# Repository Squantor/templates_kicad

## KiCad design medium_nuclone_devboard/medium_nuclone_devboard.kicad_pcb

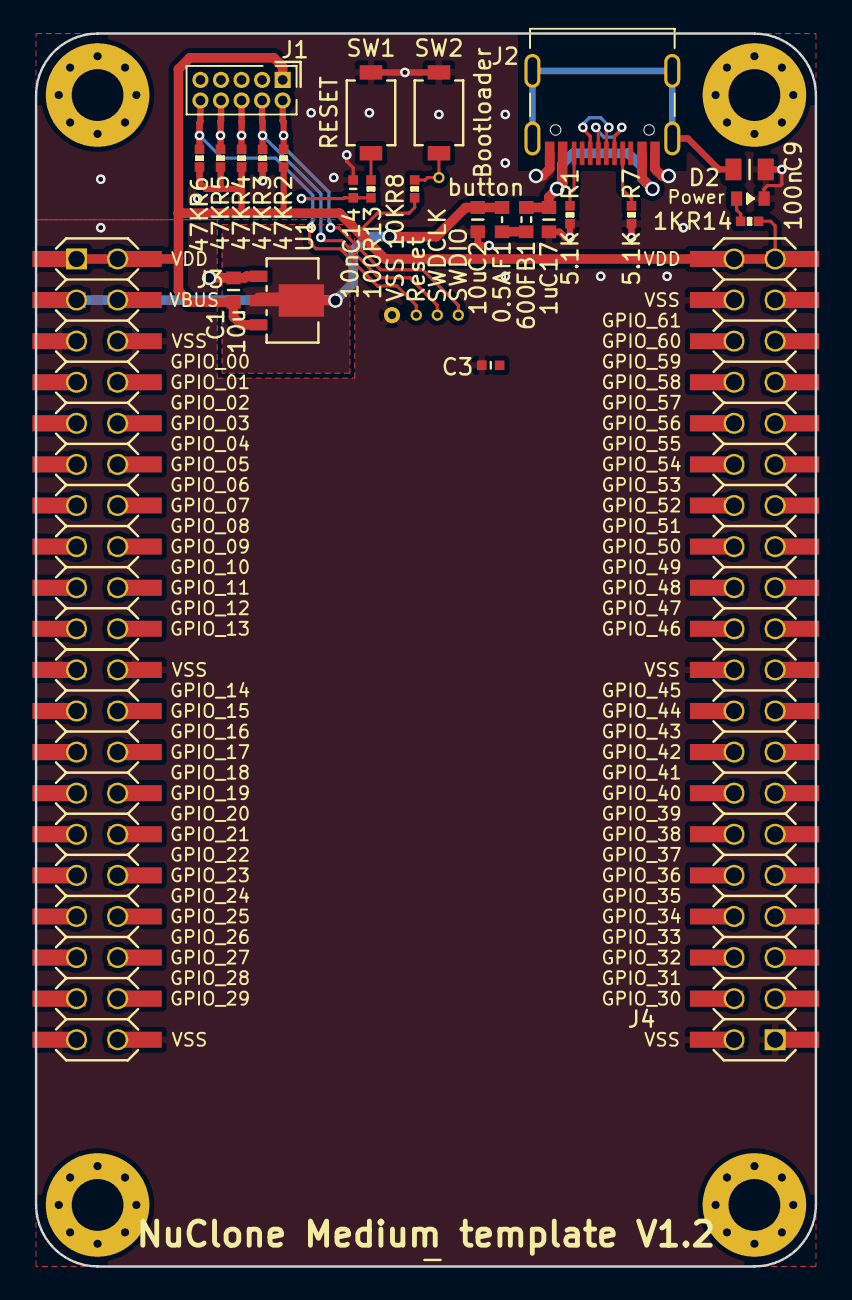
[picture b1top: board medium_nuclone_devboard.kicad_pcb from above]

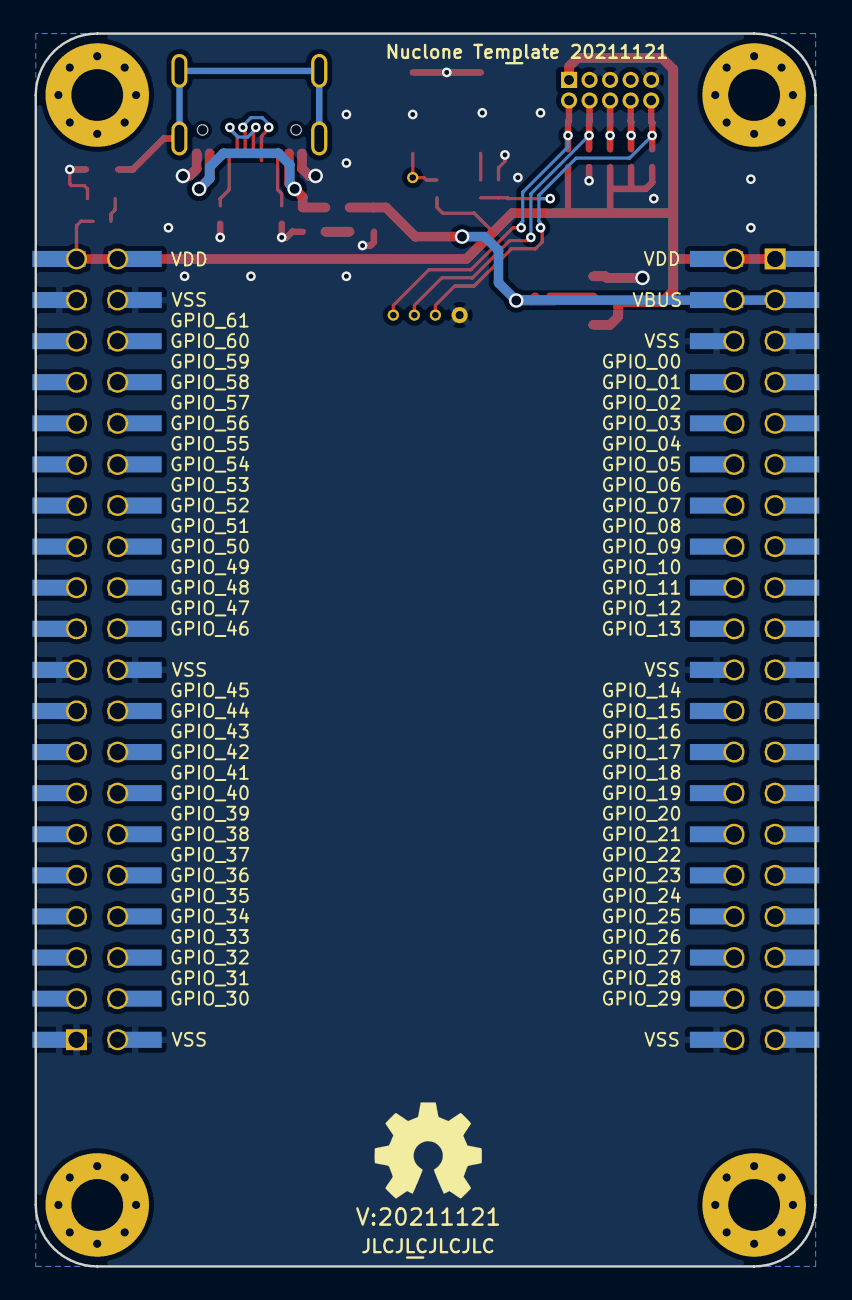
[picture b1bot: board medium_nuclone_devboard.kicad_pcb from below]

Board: 2 copper layers, 48.2 x 76.2 mm, 40 parts (4 on the bottom side), 18 nets.

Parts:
C1, C2: 10u; C_0603
C3: 1u; C_0402
C9: 100n; C_0805
C14: 10n; C_0402
C17: 1u; C_0603
D2: GREEN; LED_0603_hand
F1: 0.5A; F_0603_hand
FB1: 600; L_0603
H1, H2, H3, H4: MountingHole; MountingHole_3.2mm_M3_Pad_Via
J1: JTAG_2X05; Header-0127-2X05-H006
J2: TYPE-C-31-M-12; USB-C-HRO-31-M-12
J3: nuclone_medium_left; nuclone_medium_left_stacked
J4: nuclone_medium_right; nuclone_medium_right_stacked
N1: OHWLOGO; OSHW-Symbol_6.7x6mm_SilkScreen
N2: 20211121; Label_version
N3: JLCJLCJLCJLC; Label_Generic
N4: NuClone Medium template V1.2; Label_Generic
N5: Nuclone Template 20211121; Label_Generic
R1, R7: 5.1K; R_0402_hand
R2, R3, R4, R5, R6: 47K; R_0402_hand
R8: 10K; R_0402_hand
R13: 100; R_0402_hand
R14: 1K; R_0402_hand
SW1: RESET; TD-85XU
SW2: Bootloader; TD-85XU
TP1: SWDIO; TestPoint_hole_H04R07
TP2: SWDCLK; TestPoint_hole_H04R07
TP3: VSS; TestPoint_hole_H05R10
TP4: button; TestPoint_hole_H04R07
TP5: Reset; TestPoint_hole_H04R07
U1: MCP1702-MB; SOT89-NXP

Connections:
/Bootloader: R8.1, SW2.2, TP4.1
/RESET: C14.2, J1.10, R6.1, R13.1, TP5.1
/TCK: J1.4, R3.1, TP2.1
/TDI: J1.8, R5.1
/TDO: J1.6, R4.1
/TMS: J1.2, R2.1, TP1.1
/VBUS: C2.2, F1.1, J3.3, J3.4, U1.2
/VDD: C1.1, C3.1, J1.1, J3.1, J3.2, J4.39, J4.40, R2.2, R4.2, R5.2, R6.2, R8.2, R14.2, U1.3
/VSS: C1.2, C2.1, C3.2, C9.1, C14.1, C17.1, D2.1, J1.3, J1.5, J1.9, J2.A1B12, J2.B1A12, J3.5, J3.6, J3.21, J3.22, J3.39, J3.40, J4.1, J4.2, J4.19, J4.20, J4.37, J4.38, R1.1, R3.2, R7.1, SW1.1, SW2.1, TP3.1, U1.1
unnamed: C9.2, J2.S
unnamed: C17.2, FB1.2, J2.A4B9, J2.B4A9
unnamed: D2.2, R14.1
unnamed: F1.2, FB1.1
unnamed: J2.A5, R7.2
unnamed: J2.A6, J2.B6
unnamed: J2.A7, J2.B7
unnamed: J2.B5, R1.2
unnamed: R13.2, SW1.2

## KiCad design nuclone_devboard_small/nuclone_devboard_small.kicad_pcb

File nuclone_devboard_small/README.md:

# Nuclone development board template for low pincount microcontrollers
Small development board inspired by the nucleo series from STM32.
## TODO's
Still some things need to be done:
* proper description(TODO)
* schematic entry (TODO)
* PCB layout (TODO)
* Review with one night in between (TODO)
* Produce at [OSHPARK](https://oshpark.com/) (TODO)
* Assemble (TODO)
* Test & characterise (TODO)
* update Readme.md with pictures and BOM (TODO)

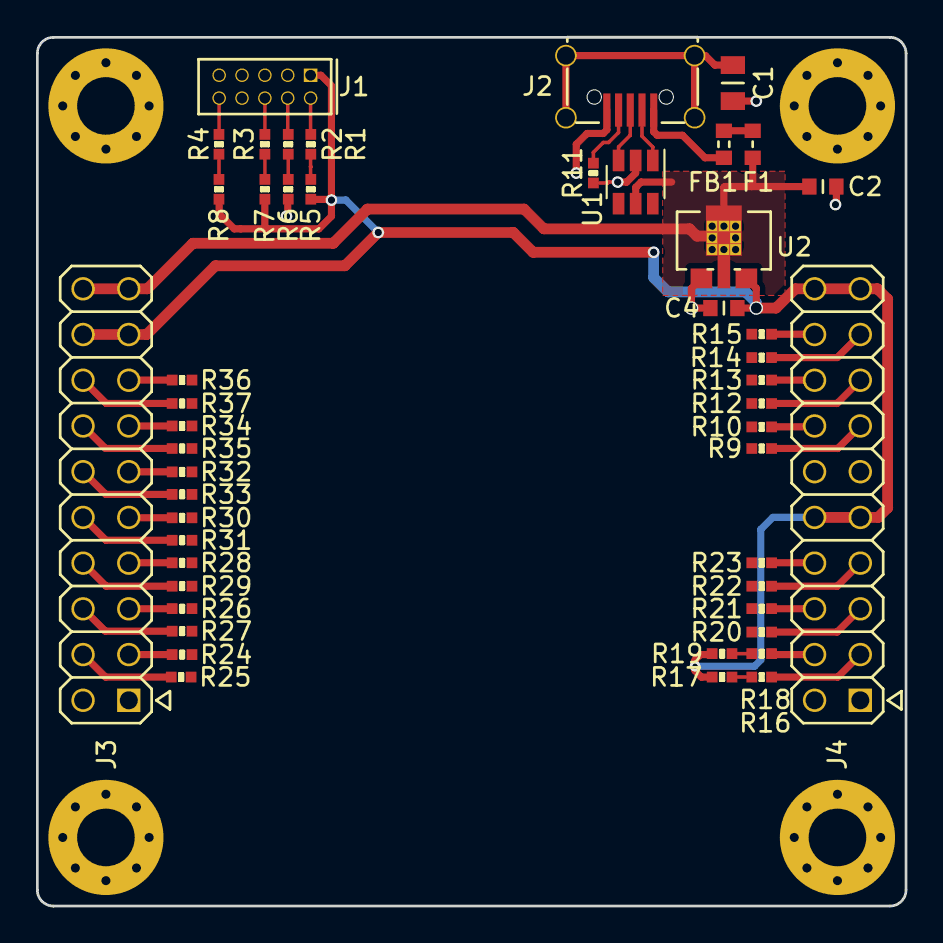
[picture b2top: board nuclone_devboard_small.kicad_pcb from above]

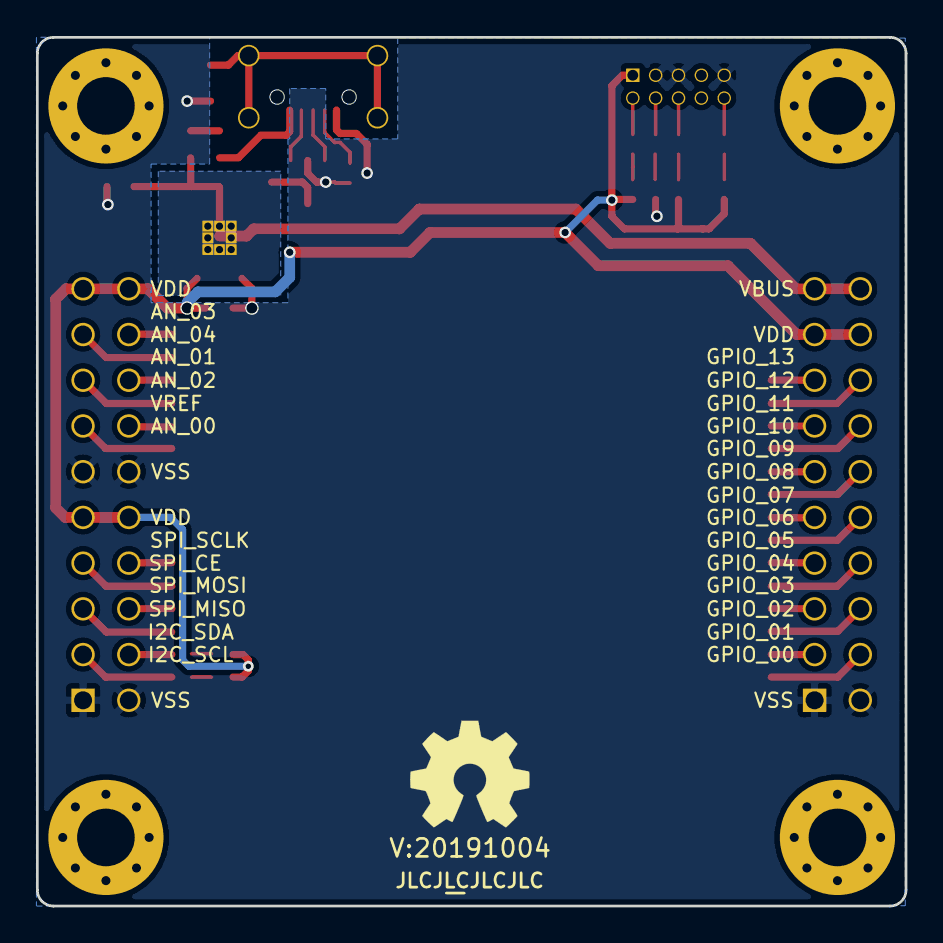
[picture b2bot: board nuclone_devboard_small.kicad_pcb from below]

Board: 2 copper layers, 48.3 x 48.3 mm, 55 parts (3 on the bottom side), 45 nets.

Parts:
C1: 100n; C_0805
C2, C4: 10u; C_0603
F1: 0.5A; F_0603_hand
FB1: 100; L_0603
H1, H2, H3, H4: MountingHole; MountingHole_3.2mm_M3_Pad_Via
J1: JTAG_2X05; Header-0127-2X05-H006
J2: USB-ID; USB-muB-SMD_TH
J3: nuclone_20pin_gpio; Nuclone_20pin_gpio
J4: nuclone_20pin_bus_analog; Nuclone_20pin_bus_analog
N1: OHWLOGO; OSHW-Symbol_6.7x6mm_SilkScreen
N2: 20191004; Label_version
N3: JLCJLCJLCJLC; Label_Generic
R1, R2, R3, R4, R9, R10, R12, R13, R14, R15, R16, R18, R20, R21, R22, R23, R24, R25, R26, R27, R28, R29, R30, R31, R32, R33, R34, R35, R36, R37: 100; R_0402_hand
R5: 100K; R_0402_hand
R6, R7, R8: 100k; R_0402_hand
R11: 0; R_0402_hand
R17, R19: 2.2K; R_0402_hand
U1: USBLC6-2; SOT23-6-HAND
U2: MCP1702-MB; SOT89-SOT23-Dual-NXP

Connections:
/AN_00: J4.14, R10.2
/AN_01: J4.15, R12.2
/AN_02: J4.16, R13.2
/AN_03: J4.17, R14.2
/AN_04: J4.18, R15.2
/GPIO_00: J3.3, R24.2
/GPIO_01: J3.4, R25.2
/GPIO_02: J3.5, R26.2
/GPIO_03: J3.6, R27.2
/GPIO_04: J3.7, R28.2
/GPIO_05: J3.8, R29.2
/GPIO_06: J3.9, R30.2
/GPIO_07: J3.10, R31.2
/GPIO_08: J3.11, R32.2
/GPIO_09: J3.12, R33.2
/GPIO_10: J3.13, R34.2
/GPIO_11: J3.14, R35.2
/GPIO_12: J3.15, R36.2
/GPIO_13: J3.16, R37.2
/I2C_SCL: J4.4, R18.2
/I2C_SCL_INT: R18.1, R19.1
/I2C_SDA: J4.3, R16.2
/I2C_SDA_INT: R16.1, R17.1
/RESET: R4.2, R8.2
/SPI_CE: J4.8, R23.2
/SPI_MISO: J4.6, R21.2
/SPI_MOSI: J4.5, R20.2
/SPI_SCLK: J4.7, R22.2
/TCK: R2.2, R6.2
/TDO: R3.2, R7.2
/TMS: R1.2, R5.2
/USB_IN_D+: J2.3, U1.3
/USB_IN_D-: J2.2, U1.1
/VBUS: C2.1, F1.1, J3.19, J3.20, U1.5, U2.2
/VDD: C4.1, J1.1, J3.17, J3.18, J4.9, J4.10, J4.19, J4.20, R5.1, R7.1, R8.1, R17.2, R19.2, U2.3
/VREF: J4.13, R9.2
/VSS: C1.2, C2.2, C4.2, J1.3, J1.5, J1.9, J2.5, J3.1, J3.2, J4.1, J4.2, J4.11, J4.12, R6.1, R11.1, U1.2, U2.1
unnamed: C1.1, J2.S
unnamed: F1.2, FB1.1
unnamed: FB1.2, J2.1
unnamed: J1.2, R1.1
unnamed: J1.4, R2.1
unnamed: J1.6, R3.1
unnamed: J1.10, R4.1
unnamed: J2.4, R11.2

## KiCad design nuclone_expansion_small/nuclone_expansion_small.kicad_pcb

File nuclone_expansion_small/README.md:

# $(HARDWARE_PROJECT) project
Project description goes here.
# HSI (Hardware Software Interface)
This applies to a project that has a embedded software component. Describe what each pin/bus does, what it is connected to, what its function is and some "safe" behaviour when starting up.
## TODO's
Still some things need to be done:
* Fill in this project description
* schematic entry 
* PCB layout
* Review with one night in between
* Produce at [OSHPARK](https://oshpark.com/)
* Assemble
* Test & characterise
* update Readme.md with pictures and BOM
## BOM
This is a list of hardware components. If just mentioned a generic component like a 1K 0402 resistor, just name it as such, free to substitute. If you need some special integrated IC's show some sources like Mouser, Digikey, Farnell, or LCSC
* Generic resistor in 0402 housing with a value
* Generic capacitor in 0603 housing with a value
* Special IC from [LCSC](https://lcsc.com/)
## Pictures

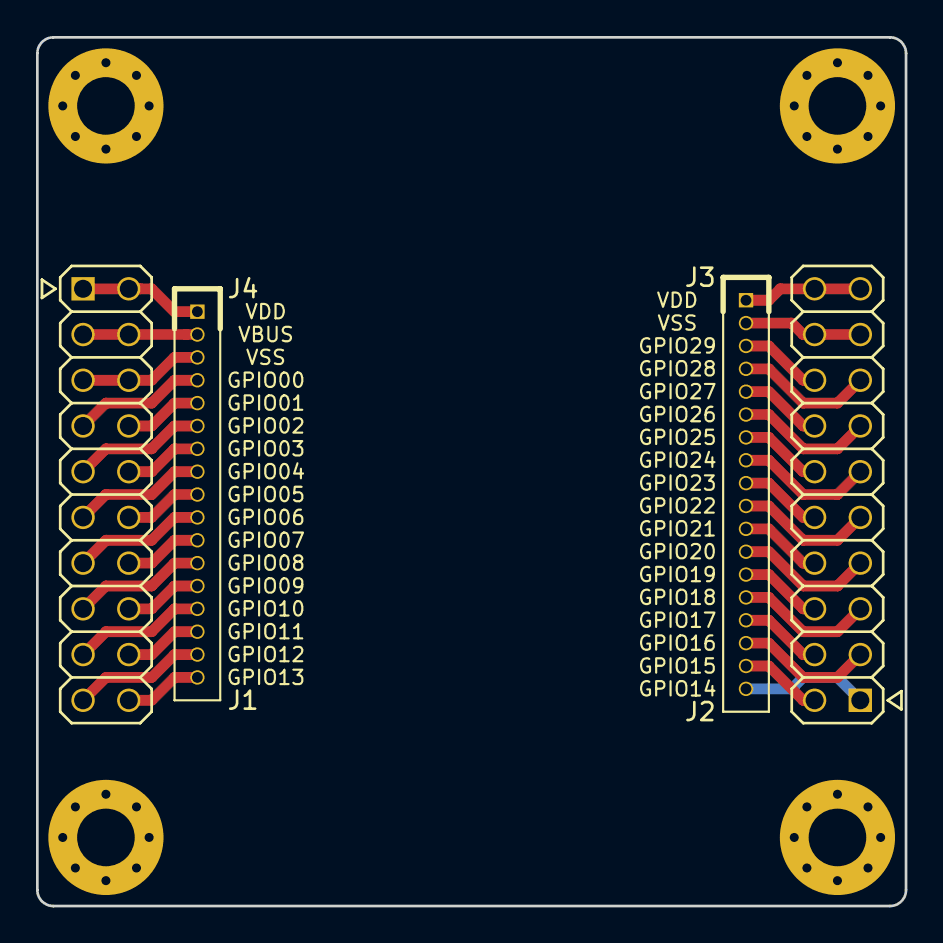
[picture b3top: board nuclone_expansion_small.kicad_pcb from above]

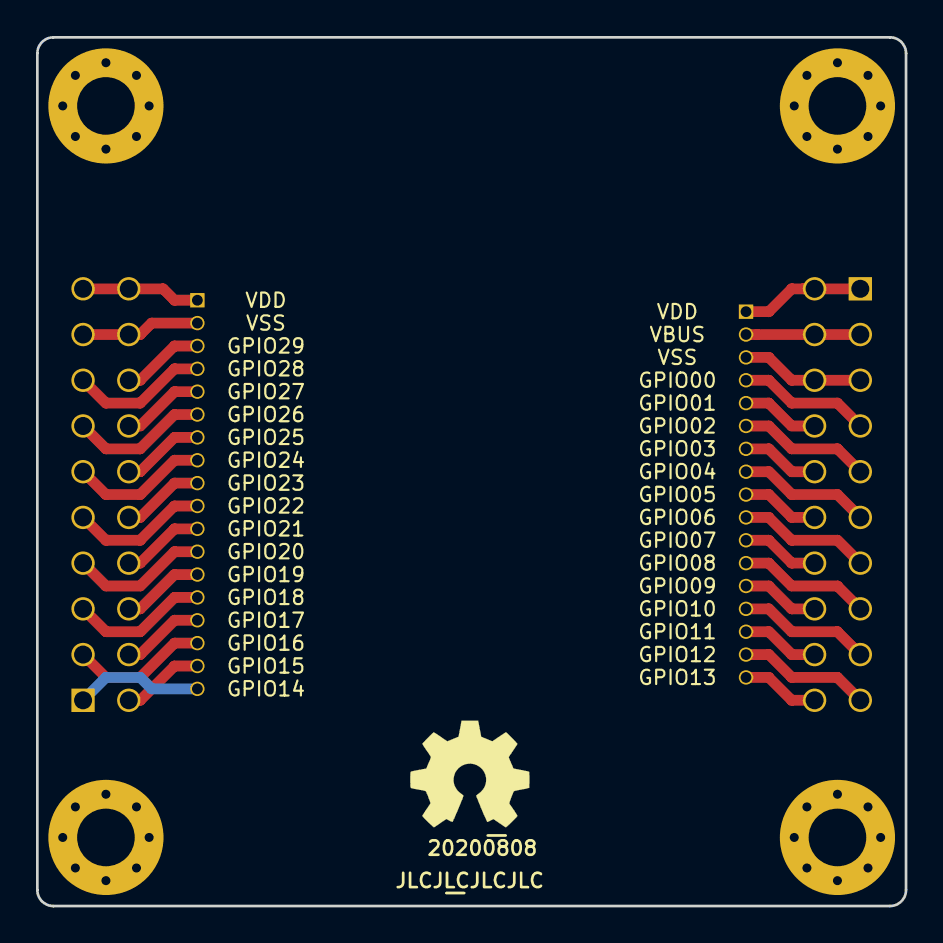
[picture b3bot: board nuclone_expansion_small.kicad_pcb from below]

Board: 2 copper layers, 48.3 x 48.3 mm, 11 parts (3 on the bottom side), 35 nets.

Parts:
H1, H2, H3, H4: MountingHole; MountingHole_3.2mm_M3_Pad_Via
J1: nuclone_small_left; Header-0254-2X10-H010
J2: nuclone_small_right; Header-0254-2X10-H010
J3: PINS_1X18; Header-0127-1X18-H006
J4: PINS_1X17; Header-0127-1X17-H006
N1: OHWLOGO; OSHW-Symbol_6.7x6mm_SilkScreen
N2: 20200808; Label_Generic
N3: JLCJLCJLCJLC; Label_Generic

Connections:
/GPIO_00: J1.7, J4.4
/GPIO_01: J1.8, J4.5
/GPIO_02: J1.9, J4.6
/GPIO_03: J1.10, J4.7
/GPIO_04: J1.11, J4.8
/GPIO_05: J1.12, J4.9
/GPIO_06: J1.13, J4.10
/GPIO_07: J1.14, J4.11
/GPIO_08: J1.15, J4.12
/GPIO_09: J1.16, J4.13
/GPIO_10: J1.17, J4.14
/GPIO_11: J1.18, J4.15
/GPIO_12: J1.19, J4.16
/GPIO_13: J1.20, J4.17
/GPIO_14: J2.1, J3.18
/GPIO_15: J2.2, J3.17
/GPIO_16: J2.3, J3.16
/GPIO_17: J2.4, J3.15
/GPIO_18: J2.5, J3.14
/GPIO_19: J2.6, J3.13
/GPIO_20: J2.7, J3.12
/GPIO_21: J2.8, J3.11
/GPIO_22: J2.9, J3.10
/GPIO_23: J2.10, J3.9
/GPIO_24: J2.11, J3.8
/GPIO_25: J2.12, J3.7
/GPIO_26: J2.13, J3.6
/GPIO_27: J2.14, J3.5
/GPIO_28: J2.15, J3.4
/GPIO_29: J2.16, J3.3
/VBUS: J1.3, J1.4, J4.2
/VDD1: J1.1, J1.2, J4.1
/VDD2: J2.19, J2.20, J3.1
/VSS1: J1.5, J1.6, J4.3
/VSS2: J2.17, J2.18, J3.2

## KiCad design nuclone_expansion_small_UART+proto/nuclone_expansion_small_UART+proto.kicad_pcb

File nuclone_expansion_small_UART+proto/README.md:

# Nuclone expansion board
Nuclone expansion board with UART connector and pin test pads, basis for many development boards
# HSI (Hardware Software Interface)
This applies to a project that has a embedded software component. Describe what each pin/bus does, what it is connected to, what its function is and some "safe" behaviour when starting up.
## TODO's
Still some things need to be done:
* schematic entry 
* Fill in HSI
* PCB layout
* Review with one night in between
* Produce at [Aisler](https://aisler.net/)
* Assemble
* Test & characterise
* update Readme.md with pictures and BOM
## BOM
This is a list of hardware components. If just mentioned a generic component like a 1K 0402 resistor, just name it as such, free to substitute. If you need some special integrated IC's show some sources like Mouser, Digikey, Farnell, or LCSC

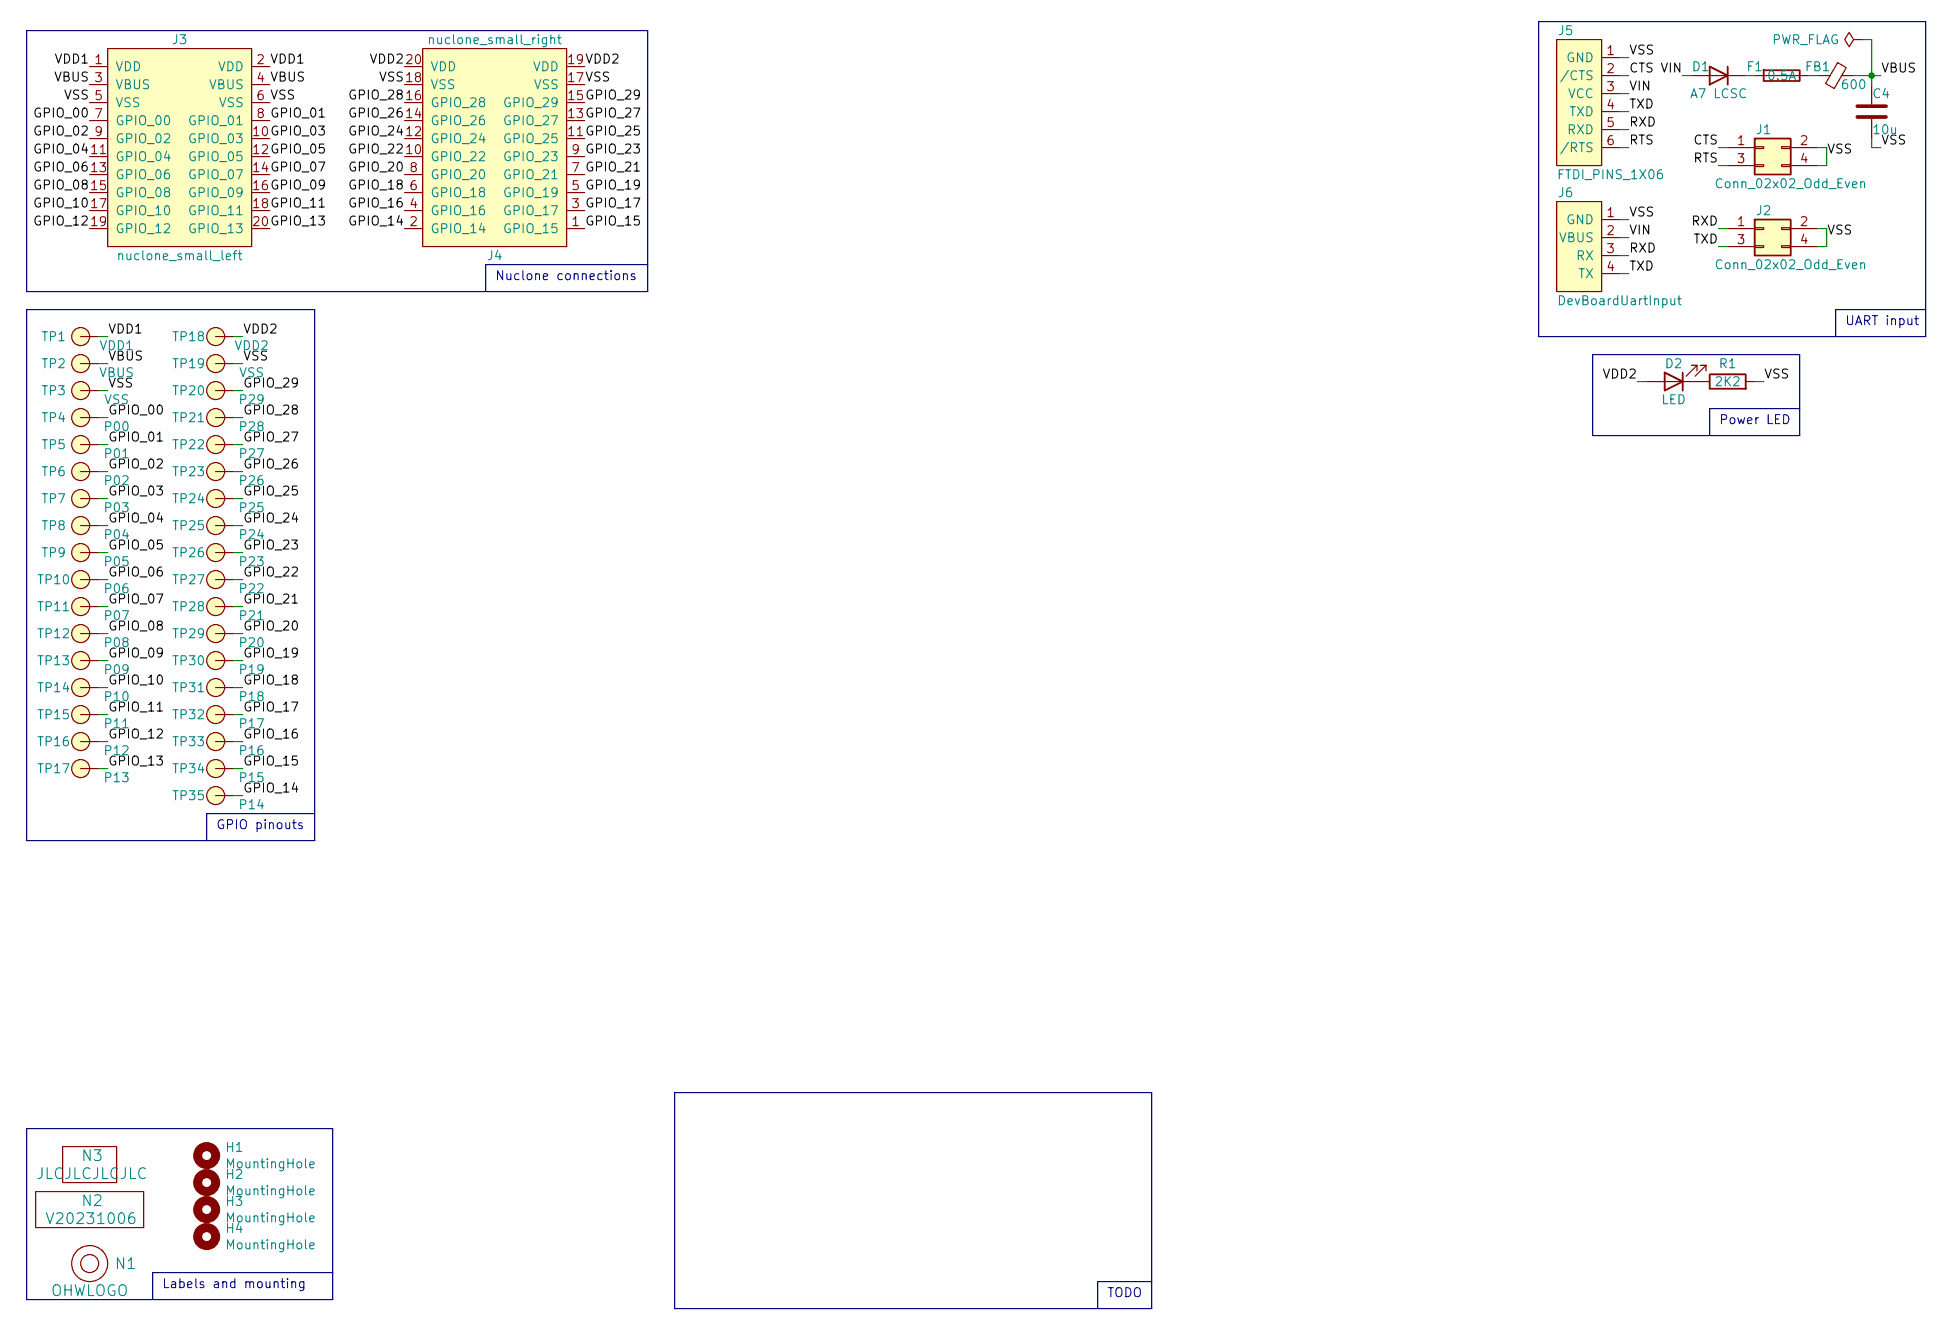
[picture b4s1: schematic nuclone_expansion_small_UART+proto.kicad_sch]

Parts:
C4: 10u; C_0603
D1: A7 LCSC; SOD-123F-hand
D2: LED; LED_0603_hand
F1: 0.5A; F_0603_hand
FB1: 600; L_0603
H1, H2, H3, H4: MountingHole; MountingHole_3.2mm_M3_Pad_Via
J1, J2: Conn_02x02_Odd_Even; Header-0254-2X02-H010
J3: nuclone_small_left; nuclone_small_left_stacked
J4: nuclone_small_right; nuclone_small_right_stacked
J5: FTDI_PINS_1X06; Header-0254-1X06-H010
J6: DevBoardUartInput; JST_PH_B4B-PH-K_1x04_P2.00mm_Vertical
N1: OHWLOGO; OSHW-Symbol_6.7x6mm_SilkScreen
N2: V20231006; Label_Generic
N3: JLCJLCJLCJLC; Label_Generic
R1: 2K2; R_0603_hand
TP1: VDD1; TestPoint_hole_H05R10_2side
TP2: VBUS; TestPoint_hole_H05R10_2side
TP3, TP19: VSS; TestPoint_hole_H05R10_2side
TP4: P00; TestPoint_hole_H05R10_2side
TP5: P01; TestPoint_hole_H05R10_2side
TP6: P02; TestPoint_hole_H05R10_2side
TP7: P03; TestPoint_hole_H05R10_2side
TP8: P04; TestPoint_hole_H05R10_2side
TP9: P05; TestPoint_hole_H05R10_2side
TP10: P06; TestPoint_hole_H05R10_2side
TP11: P07; TestPoint_hole_H05R10_2side
TP12: P08; TestPoint_hole_H05R10_2side
TP13: P09; TestPoint_hole_H05R10_2side
TP14: P10; TestPoint_hole_H05R10_2side
TP15: P11; TestPoint_hole_H05R10_2side
TP16: P12; TestPoint_hole_H05R10_2side
TP17: P13; TestPoint_hole_H05R10_2side
TP18: VDD2; TestPoint_hole_H05R10_2side
TP20: P29; TestPoint_hole_H05R10_2side
TP21: P28; TestPoint_hole_H05R10_2side
TP22: P27; TestPoint_hole_H05R10_2side
TP23: P26; TestPoint_hole_H05R10_2side
TP24: P25; TestPoint_hole_H05R10_2side
TP25: P24; TestPoint_hole_H05R10_2side
TP26: P23; TestPoint_hole_H05R10_2side
TP27: P22; TestPoint_hole_H05R10_2side
TP28: P21; TestPoint_hole_H05R10_2side
TP29: P20; TestPoint_hole_H05R10_2side
TP30: P19; TestPoint_hole_H05R10_2side
TP31: P18; TestPoint_hole_H05R10_2side
TP32: P17; TestPoint_hole_H05R10_2side
TP33: P16; TestPoint_hole_H05R10_2side
TP34: P15; TestPoint_hole_H05R10_2side
TP35: P14; TestPoint_hole_H05R10_2side

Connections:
/CTS: J1.1, J5.2 (/CTS)
/GPIO_00: J3.7 (GPIO_00), TP4.1
/GPIO_01: J3.8 (GPIO_01), TP5.1
/GPIO_02: J3.9 (GPIO_02), TP6.1
/GPIO_03: J3.10 (GPIO_03), TP7.1
/GPIO_04: J3.11 (GPIO_04), TP8.1
/GPIO_05: J3.12 (GPIO_05), TP9.1
/GPIO_06: J3.13 (GPIO_06), TP10.1
/GPIO_07: J3.14 (GPIO_07), TP11.1
/GPIO_08: J3.15 (GPIO_08), TP12.1
/GPIO_09: J3.16 (GPIO_09), TP13.1
/GPIO_10: J3.17 (GPIO_10), TP14.1
/GPIO_11: J3.18 (GPIO_11), TP15.1
/GPIO_12: J3.19 (GPIO_12), TP16.1
/GPIO_13: J3.20 (GPIO_13), TP17.1
/GPIO_14: J4.2 (GPIO_14), TP35.1
/GPIO_15: J4.1 (GPIO_15), TP34.1
/GPIO_16: J4.4 (GPIO_16), TP33.1
/GPIO_17: J4.3 (GPIO_17), TP32.1
/GPIO_18: J4.6 (GPIO_18), TP31.1
/GPIO_19: J4.5 (GPIO_19), TP30.1
/GPIO_20: J4.8 (GPIO_20), TP29.1
/GPIO_21: J4.7 (GPIO_21), TP28.1
/GPIO_22: J4.10 (GPIO_22), TP27.1
/GPIO_23: J4.9 (GPIO_23), TP26.1
/GPIO_24: J4.12 (GPIO_24), TP25.1
/GPIO_25: J4.11 (GPIO_25), TP24.1
/GPIO_26: J4.14 (GPIO_26), TP23.1
/GPIO_27: J4.13 (GPIO_27), TP22.1
/GPIO_28: J4.16 (GPIO_28), TP21.1
/GPIO_29: J4.15 (GPIO_29), TP20.1
/RTS: J1.3, J5.6 (/RTS)
/RXD: J2.1, J5.5 (RXD), J6.3 (RX)
/TXD: J2.3, J5.4 (TXD), J6.4 (TX)
/VBUS: C4.1, FB1.1, J3.3 (VBUS), J3.4 (VBUS), TP2.1
/VDD1: J3.1 (VDD), J3.2 (VDD), TP1.1
/VDD2: D2.2 (A), J4.19 (VDD), J4.20 (VDD), TP18.1
/VIN: D1.2 (A), J5.3 (VCC), J6.2 (VBUS)
/VSS: C4.2, J1.2, J1.4, J2.2, J2.4, J3.5 (VSS), J3.6 (VSS), J4.17 (VSS), J4.18 (VSS), J5.1 (GND), J6.1 (GND), R1.2, TP3.1, TP19.1
unnamed: D1.1 (K), F1.2
unnamed: D2.1 (K), R1.1
unnamed: F1.1, FB1.2

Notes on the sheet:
Labels and mounting
Power LED
TODO
GPIO pinouts
Nuclone connections
UART input

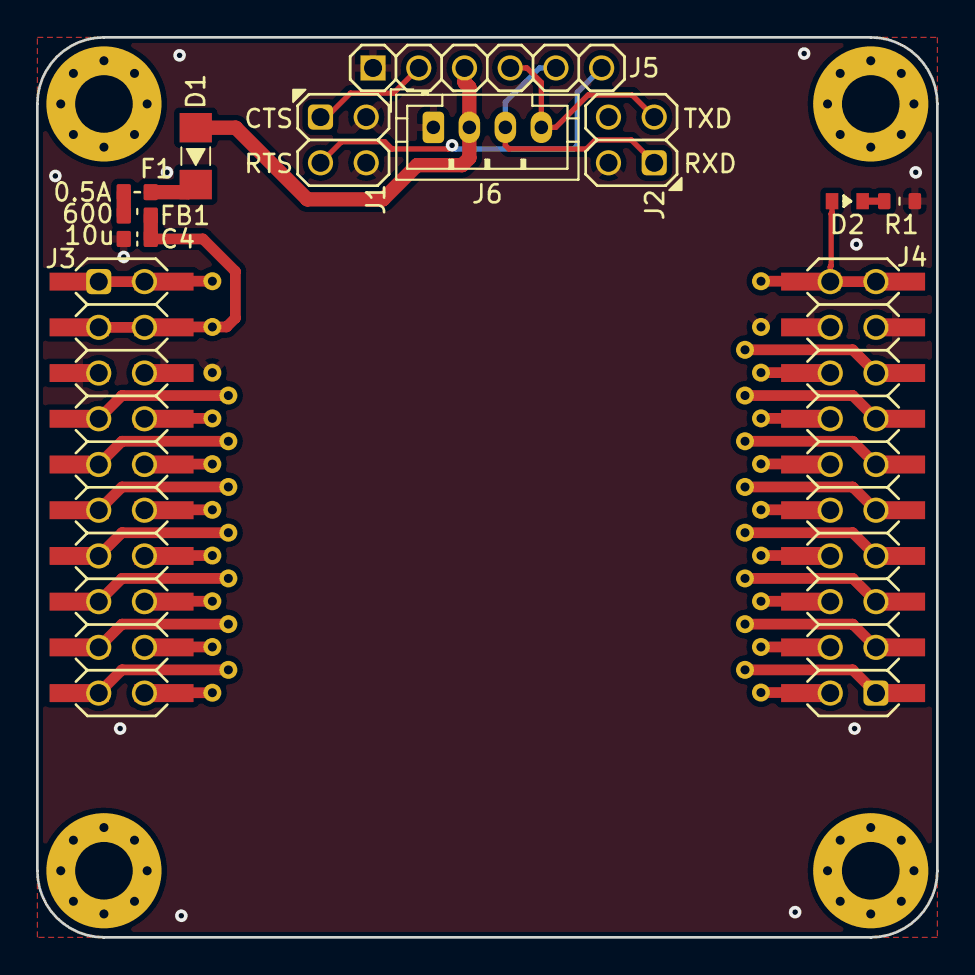
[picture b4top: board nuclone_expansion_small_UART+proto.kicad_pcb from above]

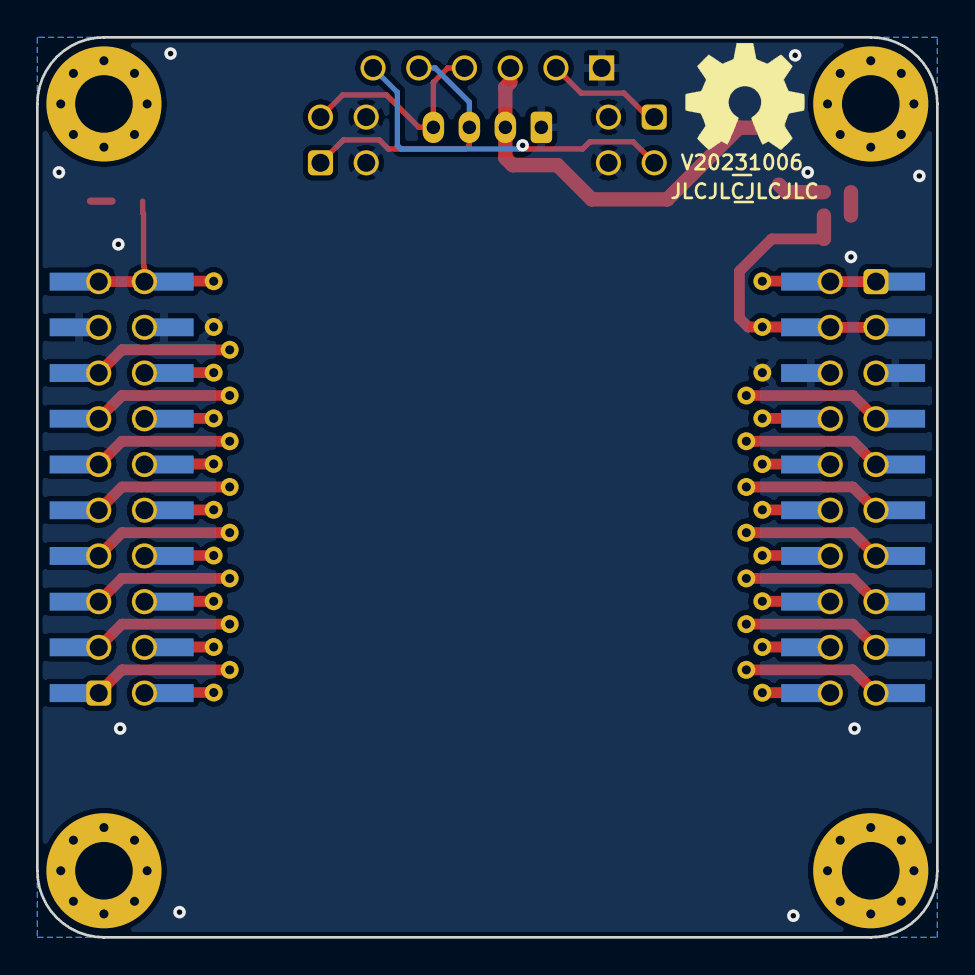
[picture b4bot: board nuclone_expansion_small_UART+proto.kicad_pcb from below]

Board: 2 copper layers, 50.0 x 50.0 mm, 54 parts (3 on the bottom side), 42 nets.
